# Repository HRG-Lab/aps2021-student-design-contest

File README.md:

# 2021 IEEE APS/URSI Student Design Contest

This repository contains the Huff Research Group's submission to the [2021 APS Student Design Contest](https://www.ieeeaps.org/education/student-design-contest), Project Artemis. The goal of this project is to demonstrate a software-defined radio (SDR) phased array architecture that performs direction of arrival (DoA) and beamforming (BF). The system will be composed of the KerberosSDR, a 4-channel coherent radio, and use a modified version of the KerberosSDR demo software to perform MUSIC spectral estimation. The focus will be building an educational toolkit that can be utilized to teach beamforming and DoA, comparing analog and digital techniques as well as hybrid analog-digital architectures.

## Motivation and Application

Radio telemetry and direction-finding methods have enabled researchers, practitioners, and citizen scientists in agriculture and biological sciences for decades. These tools are commonly used in data collection on diverse animal populations, such as tracking migratory behavior and monitoring threatened species. Coalescing this data with geotags allows scientists to infer the health of the environment and habitats where these animals reside. Recently, such techniques have been deployed to track the invasive species, _Vespa mandarinia_ (Asian giant hornet) and _Lycorma delicatula_ (spotted lanternfly), and study their impact on native ecosystems. _V. mandarinia_ can rapidly destroy entire honey bee colonies, and _L. delicatula_ can cause huge economic damage to farming and lumber industries.

The goal of Project Artemis is to design and build an extensible invasive species tracking system that utilizes an antenna array with an SDR to perform real-time DoA. Additionally, we view Artemis as a low-cost approach that lowers-the-barrier-to-entry for educators and citizen scientists to engage in the growing fields of antennas, electromagnetics, signal processing, and arrays.

## System Architecture

Above is a top-level diagram of Project Artemis detailing the interconnection between various components. The system consists of an easy-to-use software applet built-upon the KerberosSDR  project as well as custom-built, reconfigurable hardware components such as the tunable antenna elements and phase-shifter boards for hybrid beamforming. Towards the intended goal of supporting field-tracking, we have included a small display for real-time visualization and have designed the entire system to be collapsible in a ruggedized suitcase.

This shows all of the components to Artemis layed out on a table. This GitHub repository contains all of our design files as well as the source code to Artemis, and the end of this report includes the Bill of Materials. The subsections that follow describe in detail the hardware and software components.

## Artemis Software

The Artemis Software toolkit is a forked version of the KerberosSDR example toolkit, tailored for the purpose of easing usage for end-users.

## Analog Components

Fill in with information on the analog design files.

## Jupyter Teaching Notebooks

Fill in description of Jupyter notebooks to teach array processing.

## References

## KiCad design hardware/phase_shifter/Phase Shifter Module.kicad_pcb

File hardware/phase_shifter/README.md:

# Phase Shifter Modules

These modules are designed to be individually addressable fully contained phase
shifters with a full 360 degree range. This folder contains all design files.

## Schematic

## Bill of Materials

| Ref     | Value                   | Footprint                                                                       |
|---------|-------------------------|---------------------------------------------------------------------------------|
| 5V1     | Conn_01x01              | Phase Shifter Module:TestPad_Medium                                             |
| 12V1    | Conn_01x01              | Phase Shifter Module:TestPad_Medium                                             |
| C1      | 10uF                    | Capacitor_SMD:C_0805_2012Metric                                                 |
| C2      | 10uF                    | Capacitor_SMD:C_0805_2012Metric                                                 |
| D1      | PWR_LED                 | LED_SMD:LED_0805_2012Metric                                                     |
| GND1    | Conn_01x01              | Phase Shifter Module:TestPad_Medium                                             |
| IC1     | MCP4725A2T-E_CH         | Package_TO_SOT_SMD:SOT-23-6_Handsoldering                                       |
| IC2     | NCP1117ST50T3G          | NCP1117ST50T3G:SOT230P700X180-4N                                                |
| IC3     | LM741CN_NOPB            | Package_SO:SOP-8_3.9x4.9mm_P1.27mm                                              |
| J1      | Screw_Terminal_01x05    | TerminalBlock_TE-Connectivity:TerminalBlock_TE_282834-5_1x05_P2.54mm_Horizontal |
| J2      | Amphenol Edge Connector | Amphenol Edge:Amphenol_132255_Edge                                              |
| J3      | Amphenol Edge Connector | Amphenol Edge:Amphenol_132255_Edge                                              |
| J4      | Barrel_Jack             | Connector_BarrelJack:BarrelJack_CUI_PJ-063AH_Horizontal                         |
| R1      | 10k                     | Resistor_SMD:R_0805_2012Metric                                                  |
| R2      | 10k                     | Resistor_SMD:R_0805_2012Metric                                                  |
| R3      | 10k                     | Resistor_SMD:R_0805_2012Metric                                                  |
| R4      | 10k                     | Resistor_SMD:R_0805_2012Metric                                                  |
| R5      | 10k                     | Resistor_SMD:R_0805_2012Metric                                                  |
| R6      | 620                     | Resistor_SMD:R_0805_2012Metric                                                  |
| U1      | JSPHS-661+              | SamacSys_Parts:JSPHS661                                                         |
| U2      | JSPHS-661+              | SamacSys_Parts:JSPHS661                                                         |
| V_Bias1 | Conn_01x01              | Phase Shifter Module:TestPad_Medium                                             |
| V_DAC1  | Conn_01x01              | Phase Shifter Module:TestPad_Medium                                             |

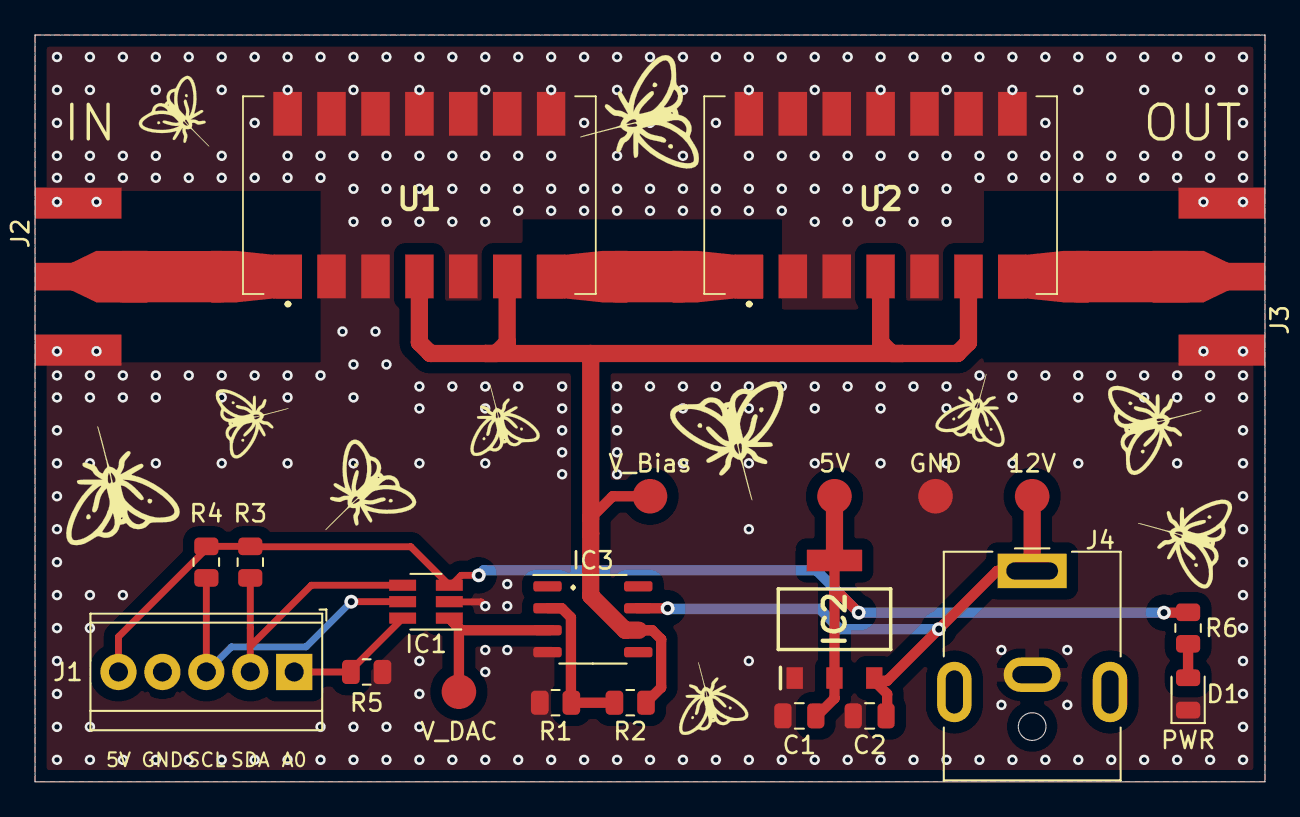
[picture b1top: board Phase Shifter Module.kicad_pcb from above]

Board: 2 copper layers, 71.1 x 43.2 mm, 31 parts (0 on the bottom side), 13 nets.

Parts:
5V1, 12V1: Conn_01x01; TestPad_Medium
Artemis: LOGO; Artemis_Logo-Large
C1, C2: 10uF; C_0805_2012Metric
D1: PWR_LED; LED_0805_2012Metric
GND1: Conn_01x01; TestPad_Medium
IC1: MCP4725A2T-E_CH; SOT-23-6_Handsoldering
IC2: NCP1117ST50T3G; SOT230P700X180-4N
IC3: LM741CN_NOPB; SOP-8_3.9x4.9mm_P1.27mm
J1: Screw_Terminal_01x05; TerminalBlock_TE_282834-5_1x05_P2.54mm_Horizontal
J2, J3: Amphenol Edge Connector; Amphenol_132255_Edge
J4: Barrel_Jack; BarrelJack_CUI_PJ-063AH_Horizontal
PSU: LOGO; PSU_Logo
R1, R2, R3, R4, R5: 10k; R_0805_2012Metric
R6: 620; R_0805_2012Metric
Taper: Signal_Pad_to_2.97mm
Taper#2: Signal_Pad_to_2.97mm
Taper#3, Taper#4, Taper#5, Taper#6: 1.5mm_to_2.97mm
U1, U2: JSPHS-661+; JSPHS661
V_Bias1: Conn_01x01; TestPad_Medium
V_DAC1: Conn_01x01; TestPad_Medium

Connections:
5V: 5V1.1, C1.1, IC1.3, IC2.2, IC2.4, J1.5, R3.2, R4.2, R6.2
12V: 12V1.1, C2.1, IC2.3, IC3.7, J4.1
A0: IC1.6, J1.1, R5.2
GND: C1.2, C2.2, D1.1, GND1.1, IC1.2, IC2.1, IC3.4, J1.4, J2.2, J3.2, J4.2, R1.2, R5.1, U1.2, U1.3, U1.5, U1.8, U1.9, U1.10, U1.11, U1.12, U1.13, U1.14, U2.2, U2.3, U2.5, U2.8, U2.9, U2.10, U2.11, U2.12, U2.13, U2.14
unnamed: D1.2, R6.1
unnamed: IC3.2, R1.1, R2.2
unnamed: Taper#5.1, Taper#6.1, U1.7, U2.1
SCL: IC1.5, J1.3, R4.1
SDA: IC1.4, J1.2, R3.1
Signal_In: J2.1, Taper#2.1, Taper#3.1, U1.1
Signal_Out: J3.1, Taper.1, Taper#4.1, U2.7
V_Bias: IC3.6, R2.1, U1.4, U1.6, U2.4, U2.6, V_Bias1.1
V_DAC: IC1.1, IC3.3, V_DAC1.1

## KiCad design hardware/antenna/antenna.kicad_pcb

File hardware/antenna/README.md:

# Antenna Design

These are the production files for the antenna. J1 and J2 are each terminal
blocks which hold a conductor (eg. copper wire). When finally assembled, this
creates a dipole antenna.

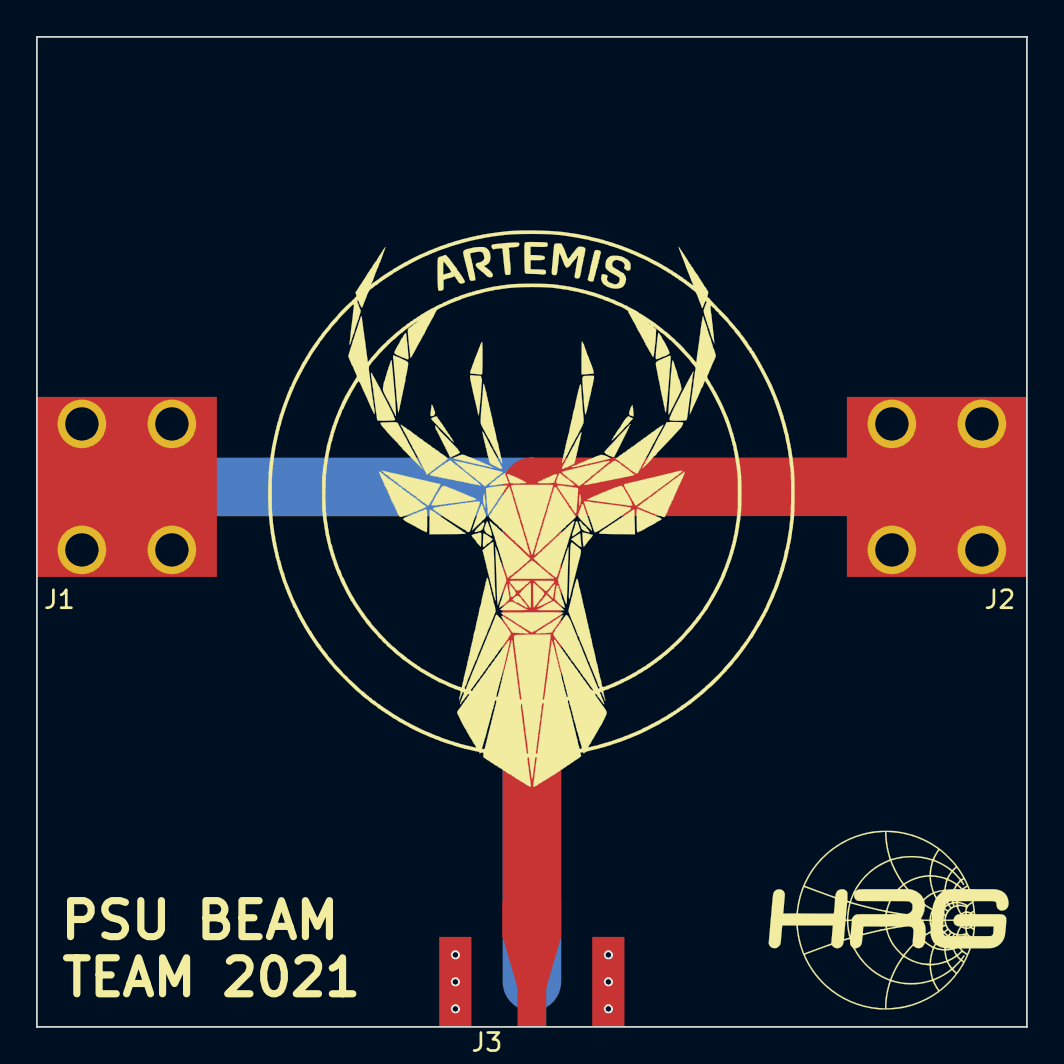
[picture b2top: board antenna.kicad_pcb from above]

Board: 2 copper layers, 55.0 x 55.0 mm, 4 parts (0 on the bottom side), 2 nets.

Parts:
J1, J2: Conn_01x01; Wire_Clamp
J3: Conn_01x02; Amphenol_132255_Edge
uwT*****: Signal_Pad_to_3.25mm

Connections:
unnamed: J1.1, J3.2
unnamed: J2.1, J3.1, uwT*****.1

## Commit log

2020-10-15 Update README.md to correct title
2021-06-03 Start creating draft of final public repository
2021-06-10 Update README.md with images and descriptions
